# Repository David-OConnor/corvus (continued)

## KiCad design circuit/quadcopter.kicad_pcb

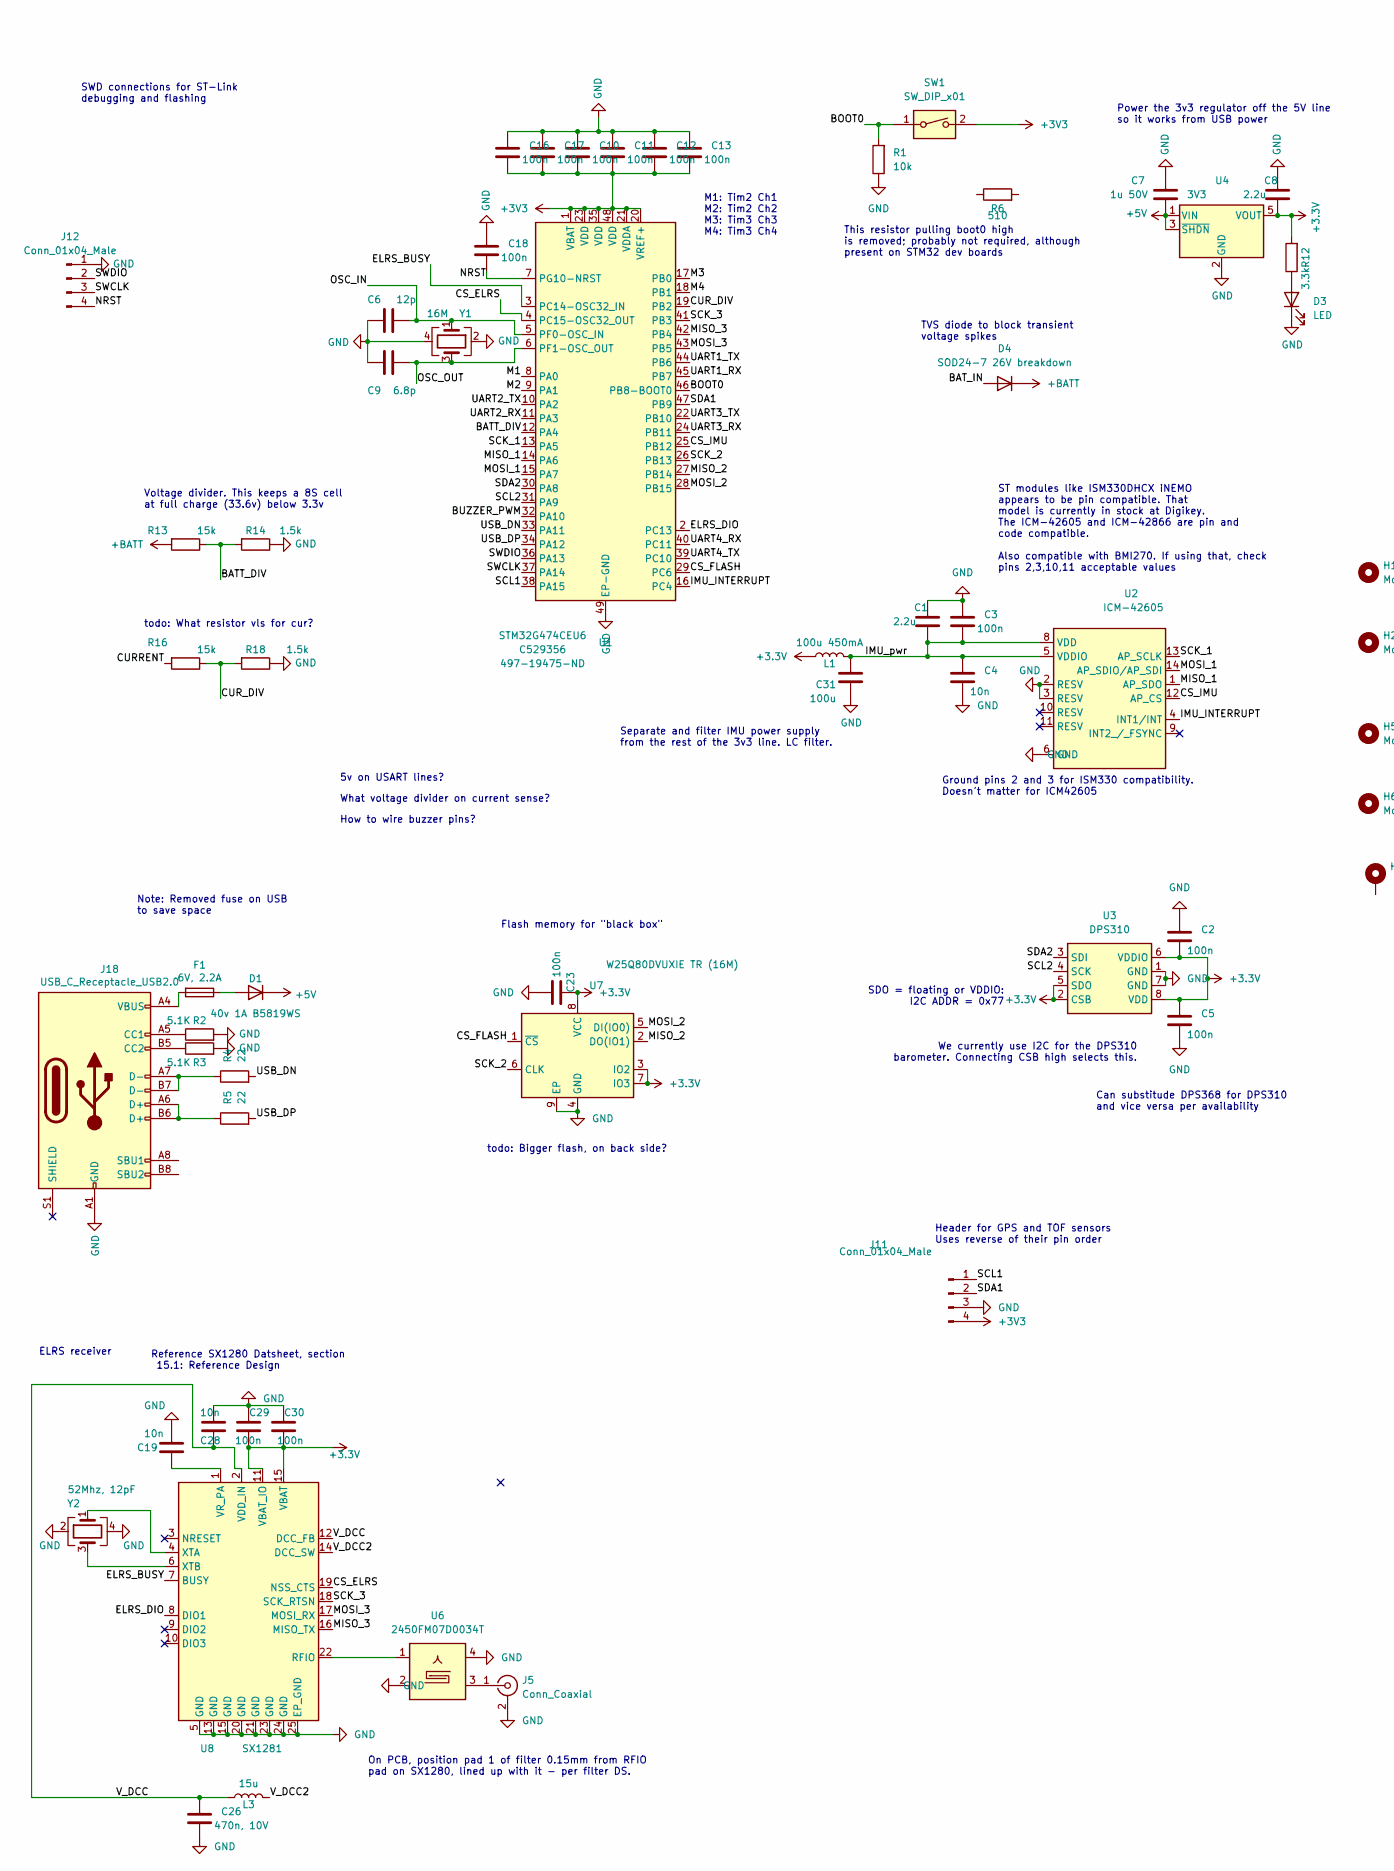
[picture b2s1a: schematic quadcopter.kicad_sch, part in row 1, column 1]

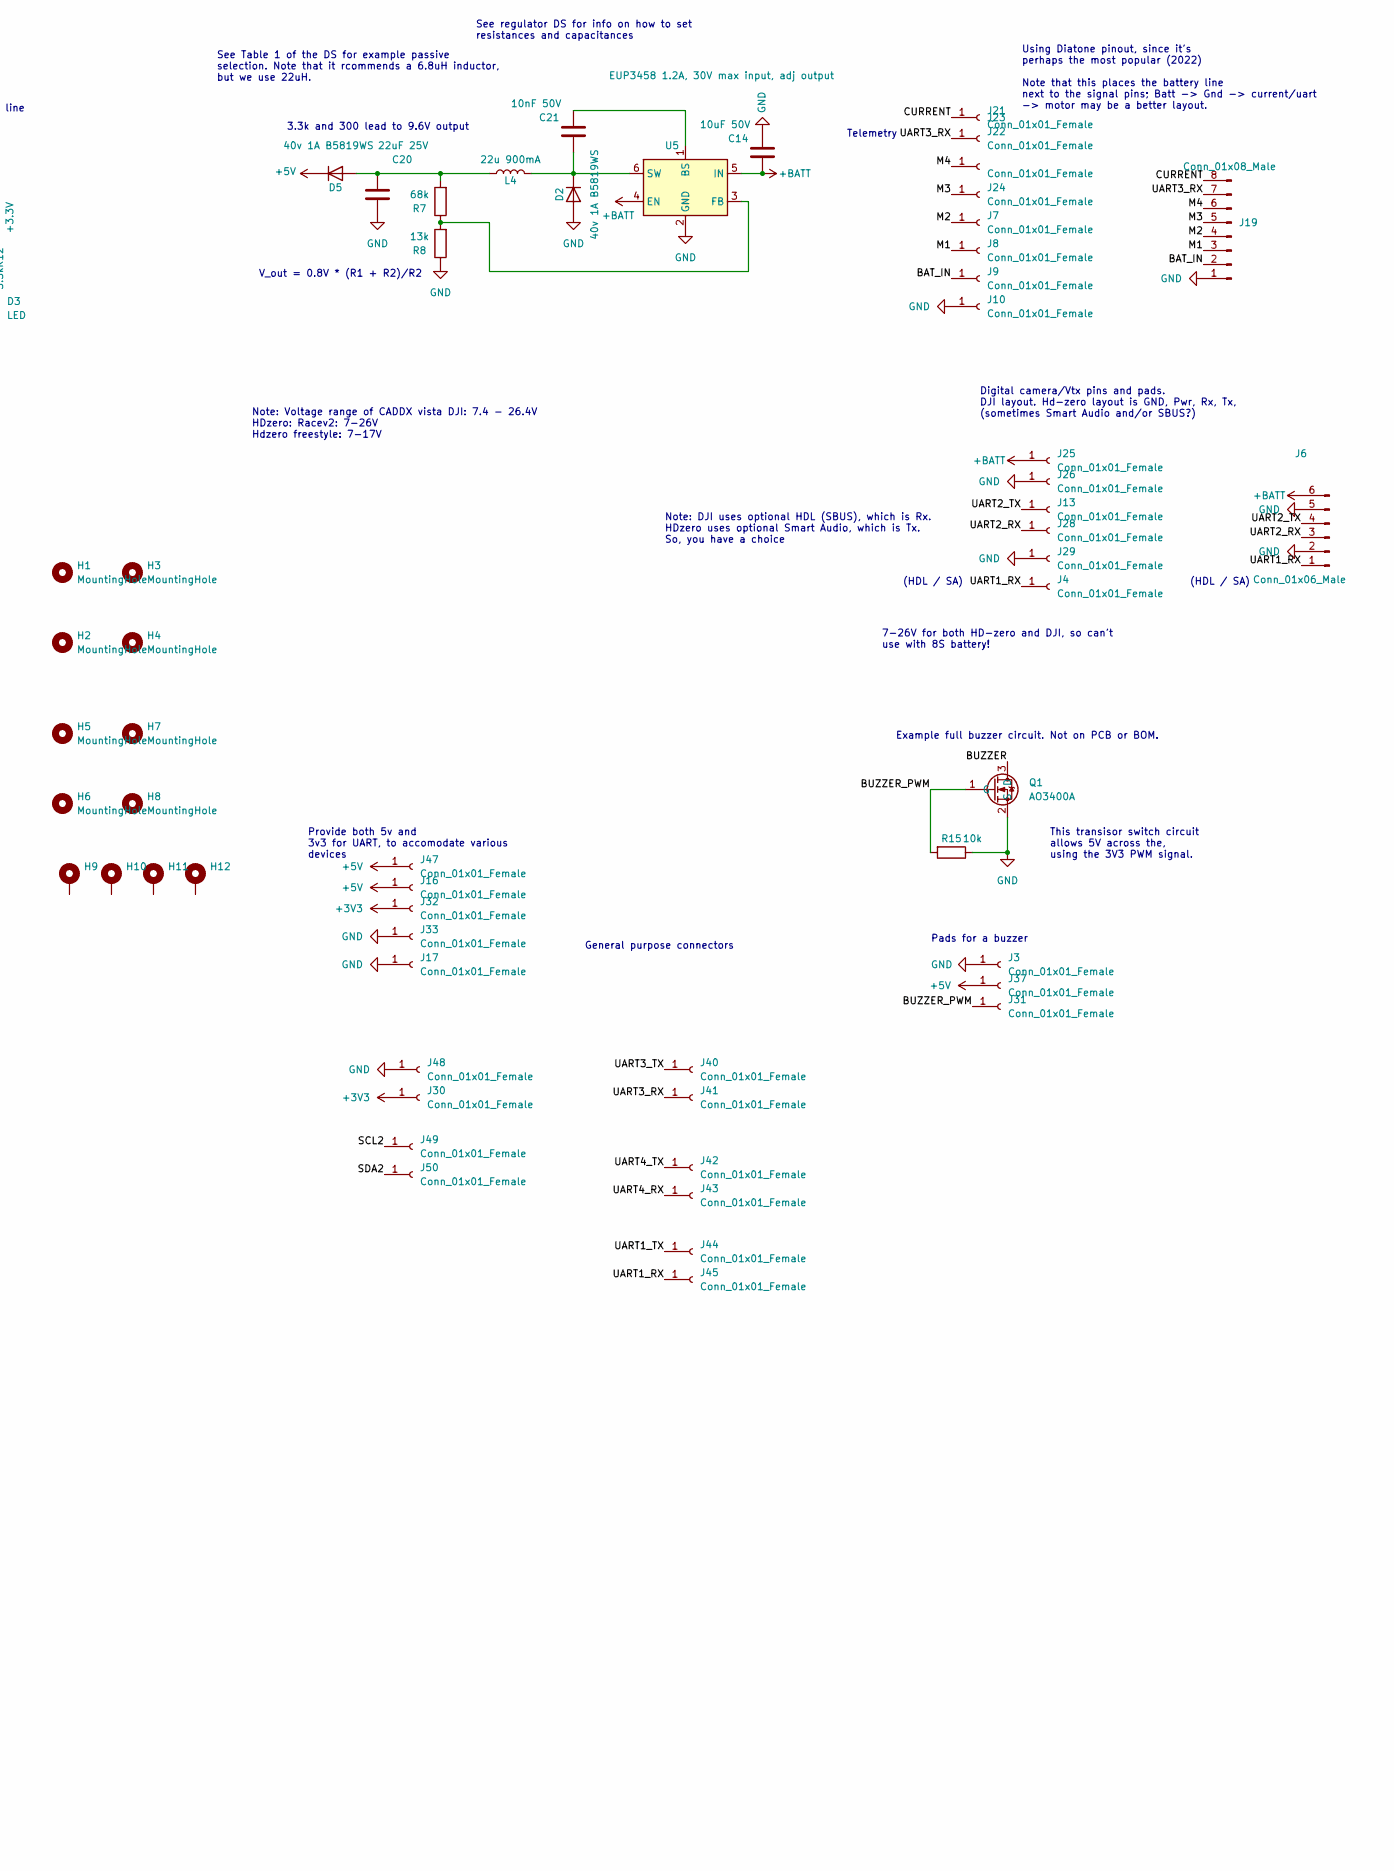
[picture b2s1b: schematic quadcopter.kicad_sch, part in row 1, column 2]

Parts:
C1, C8: 2.2u; C_0402_1005Metric; LCSC C12530
C2, C3, C5, C10, C11, C12, C13, C16, C17, C18, C23, C29, C30: 100n; C_0402_1005Metric; LCSC C1525
C4, C19, C28: 10n; C_0402_1005Metric; LCSC C15195
C6: 12p; C_0402_1005Metric; LCSC C1547
C7: 1u 50V; C_0603_1608Metric; LCSC C15849
C9: 6.8p; C_0402_1005Metric; LCSC C1576
C14: 10uF 50V; C_0805_2012Metric; LCSC C440198
C20: 22uF 25V; C_0805_2012Metric; LCSC C602037
C21: 10nF 50V; C_0402_1005Metric; LCSC C15195
C26: 470n, 10V; C_0402_1005Metric; LCSC C47339
C31: 100u; C_0805_2012Metric; LCSC C141660
D1, D2, D5: 40v 1A B5819WS; D_SOD-323; LCSC C22624
D3: LED; LED_0603_1608Metric; LCSC C205443
D4: SOD24-7 26V breakdown; D_SOD-323; Digikey 31-SD24-7TR-ND
F1: 6V, 2.2A; Fuse_0805_2012Metric; LCSC C70062
H1, H2, H3, H4, H5, H6, H7, H8: MountingHole; MountingHole_3.2mm_M3
H9, H10, H11, H12: MountingHole_Pad; Mouse bites_7mm
J3, J4, J13, J25, J26, J28, J29, J31, J37: Conn_01x01_Female; TestPoint_Pad_1.5x1.5mm
J5: Conn_Coaxial; U.FL_Hirose_U.FL-R-SMT-1_Vertical; Part Hirose U.FL-R-SMT-1(80); LCSC C88374
J6: Conn_01x06_Male; JST_SH_BM06B-SRSS-TB_1x06-1MP_P1.00mm_Vertical; LCSC C160405
J7, J8, J9, J10, J16, J17, J21, J22, J23, J24, J30, J32, J33, J40, J41, J42, J43, J44, J45, J47, J48, J49, J50: Conn_01x01_Female; TestPoint_Pad_2.0x2.0mm
J11: Conn_01x04_Male; JST_SH_SM04B-SRSS-TB_1x04-1MP_P1.00mm_Horizontal
J12: Conn_01x04_Male; JST PH staggered for 1x04 2mm
J18: USB_C_Receptacle_USB2.0; USB_C_Receptacle_XKB_U262-16XN-4BVC11; LCSC C167321
J19: Conn_01x08_Male; JST_SH_SM08B-SRSS-TB_1x08-1MP_P1.00mm_Horizontal; LCSC C160407
L1: 100u 450mA; SMNR4020 inductor; LCSC C467068
L3: 15u; L_0805_2012Metric; LCSC C154120
L4: 22u 900mA; SMNR4020 inductor; LCSC C88254
Q1: AO3400A; SOT-23; Digikey 785-1000-1-ND
R1, R15: 10k; R_0402_1005Metric; LCSC C25744
R2, R3: 5.1K; R_0402_1005Metric; LCSC C25905
R4, R5: 22; R_0402_1005Metric; LCSC C25092
R6: 510; R_0402_1005Metric; LCSC C25123
R7: 68k; R_0402_1005Metric; LCSC C36871
R8: 13k; R_0603_1608Metric; LCSC C22797
R12: 3.3k; R_0402_1005Metric; LCSC C25890
R13, R16: 15k; R_0402_1005Metric; LCSC C25756
R14, R18: 1.5k; R_0402_1005Metric; LCSC C25867
SW1: SW_DIP_x01; SW-SMD-2_3.6x6.0x8.0; LCSC C354946
U1: STM32G474CEU6; QFN-48-1EP_7x7mm_P0.5mm_EP5.6x5.6mm; LCSC C529356
U2: ICM-42605; LGA-14_3x2.5mm_P0.5mm_LayoutBorder3x4y; Digikey 1428-1152-2-ND
U3: DPS310; Bosch_LGA-8_2x2.5mm_P0.65mm_ClockwisePinNumbering; Digikey DPS310XTSA1TR-ND
U4: 3V3; TSOT-23-5; Part NATLINEAR LN1134A332MR-G; LCSC C141419
U5: EUP3458 1.2A, 30V max input, adj output; TSOT-23-6; LCSC C89300
U6: 2450FM07D0034T; 2450FM07D0034; Mouser 609-2450FM07D0034T
U7: W25Q80DVUXIE TR (16M); USON-8_2.0x3.0mm_P0.5mm; Digikey W25Q80DVUXIETR-ND
U8: SX1281; QFN-24-1EP_4x4mm_P0.5mm_EP2.6x2.6mm; Digikey SX1281IMLTRTTR-ND
Y1: 16M; Crystal_SMD_2016-4Pin_2.0x1.6mm; LCSC C254300
Y2: 52Mhz, 12pF; Crystal_SMD_3225-4Pin_3.2x2.5mm; Digikey FL520WFMT1TR-ND

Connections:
+5V: C7.2, D1.1 (K), D5.1 (K), J16.1, J37.1, J47.1, U4.1 (VIN), U4.3 (~SHDN)
+BATT: C14.2, D4.1 (K), J6.6, J25.1, R13.2, U5.4 (EN), U5.5 (IN)
/BATT_DIV: R13.1, R14.2, U1.12 (PA4)
/BAT_IN: D4.2 (A), J9.1, J19.2
/BOOT0: R1.2, SW1.1, U1.46 (PB8-BOOT0)
/BUZZER_PWM: J31.1, Q1.1 (G), R15.2, U1.32 (PA10)
/CS_ELRS: U1.4 (PC15-OSC32_OUT), U8.19 (NSS_CTS)
/CS_FLASH: U1.29 (PC6), U7.1 (~CS)
/CS_IMU: U1.25 (PB12), U2.12 (AP_CS)
/CURRENT: J19.8, J21.1, R16.2
/CUR_DIV: R16.1, R18.2, U1.19 (PB2)
/ELRS_BUSY: U1.3 (PC14-OSC32_IN), U8.7 (BUSY)
/ELRS_DIO: U1.2 (PC13), U8.8 (DIO1)
/IMU_INTERRUPT: U1.16 (PC4), U2.4 (INT1/INT)
/IMU_pwr: C1.2, C3.2, C4.1, C31.2, L1.2, U2.5 (VDDIO), U2.8 (VDD)
/M1: J8.1, J19.3, U1.8 (PA0)
/M2: J7.1, J19.4, U1.9 (PA1)
/M3: J19.5, J24.1, U1.17 (PB0)
/M4: J19.6, J23.1, U1.18 (PB1)
/MISO_1: U1.14 (PA6), U2.1 (AP_SDO)
/MISO_2: U1.27 (PB14), U7.2 (DO(IO1))
/MISO_3: U1.42 (PB4), U8.16 (MISO_TX)
/MOSI_1: U1.15 (PA7), U2.14 (AP_SDIO/AP_SDI)
/MOSI_2: U1.28 (PB15), U7.5 (DI(IO0))
/MOSI_3: U1.43 (PB5), U8.17 (MOSI_RX)
/NRST: C18.2, J12.4, U1.7 (PG10-NRST)
/OSC_IN: C6.2, U1.5 (PF0-OSC_IN), Y1.1
/OSC_OUT: C9.2, U1.6 (PF1-OSC_OUT), Y1.3
/SCK_1: U1.13 (PA5), U2.13 (AP_SCLK)
/SCK_2: U1.26 (PB13), U7.6 (CLK)
/SCK_3: U1.41 (PB3), U8.18 (SCK_RTSN)
/SCL1: J11.1, U1.38 (PA15)
/SCL2: J49.1, U1.31 (PA9), U3.4 (SCK)
/SDA1: J11.2, U1.47 (PB9)
/SDA2: J50.1, U1.30 (PA8), U3.3 (SDI)
/SWCLK: J12.3, U1.37 (PA14)
/SWDIO: J12.2, U1.36 (PA13)
/UART1_RX: J4.1, J6.1, J45.1, U1.45 (PB7)
/UART1_TX: J44.1, U1.44 (PB6)
/UART2_RX: J6.3, J28.1, U1.11 (PA3)
/UART2_TX: J6.4, J13.1, U1.10 (PA2)
/UART3_RX: J19.7, J22.1, J41.1, U1.24 (PB11)
/UART3_TX: J40.1, U1.22 (PB10)
/UART4_RX: J43.1, U1.40 (PC11)
/UART4_TX: J42.1, U1.39 (PC10)
/USB_DN: R4.2, U1.33 (PA11)
/USB_DP: R5.2, U1.34 (PA12)
/V_DCC: C26.1, C28.2, L3.1, U8.2 (VDD_IN), U8.12 (DCC_FB)
/V_DCC2: L3.2, U8.14 (DCC_SW)
unnamed: C19.2, U8.1 (VR_PA)
unnamed: C20.1, D5.2 (A), L4.1, R7.2
unnamed: C21.1, U5.1 (BS)
unnamed: C21.2, D2.1 (K), L4.2, U5.6 (SW)
unnamed: D1.2 (A), F1.1
unnamed: D3.2 (A), R12.1
unnamed: F1.2, J18.A4 (VBUS), J18.A9 (VBUS), J18.B4 (VBUS), J18.B9 (VBUS)
unnamed: J5.1 (In), U6.3
unnamed: J18.A5 (CC1), R2.1
unnamed: J18.A6 (D+), J18.B6 (D+), R5.1
unnamed: J18.A7 (D-), J18.B7 (D-), R4.1
unnamed: J18.B5 (CC2), R3.1
unnamed: R7.1, R8.2, U5.3 (FB)
unnamed: U6.1, U8.22 (RFIO)
unnamed: U8.4 (XTA), Y2.1
unnamed: U8.6 (XTB), Y2.3

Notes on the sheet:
(HDL / SA)
todo: What resistor vls for cur?
5v on USART lines?
Telemetry
3.3k and 300 lead to 9.6V output
How to wire buzzer pins?
M1: Tim2 Ch1 M2: Tim2 Ch2 M3: Tim3 Ch3 M4: Tim3 Ch4
See regulator DS for info on how to set resistances and capacitances
General purpose connectors
Voltage divider. This keeps a 8S cell at full charge (33.6v) below 3.3v
todo: Bigger flash, on back side?
Digital camera/Vtx pins and pads. DJI layout. Hd-zero layout is GND, Pwr, Rx, Tx, (sometimes Smart Audio and/or SBUS?)
Note: Removed fuse on USB to save space
On PCB, position pad 1 of filter 0.15mm from RFIO pad on SX1280, lined up with it - per filter DS.
Reference SX1280 Datsheet, section 15.1: Reference Design
We currently use I2C for the DPS310 barometer. Connecting CSB high selects this.
Separate and filter IMU power supply from the rest of the 3v3 line. LC filter.
V_out = 0.8V * (R1 + R2)/R2
This transisor switch circuit allows 5V across the, using the 3V3 PWM signal.
Provide both 5v and 3v3 for UART, to accomodate various devices
See Table 1 of the DS for example passive selection. Note that it rcommends a 6.8uH inductor, but we use 22uH.
TVS diode to block transient voltage spikes
ST modules like ISM330DHCX iNEMO appears to be pin compatible. That model is currently in stock at Digikey. The ICM-42605 and ICM-42866 are pin and code compatible. Also compatible with BMI270. If using that, check pins 2,3,10,11 acceptable values
Example full buzzer circuit. Not on PCB or BOM.
This resistor pulling boot0 high is removed; probably not required, although present on STM32 dev boards
SWD connections for ST-Link debugging and flashing
Ground pins 2 and 3 for ISM330 compatibility. Doesn't matter for ICM42605
Using Diatone pinout, since it's perhaps the most popular (2022) Note that this places the battery line next to the signal pins; Batt -> Gnd -> current/uart -> motor may be a better layout.
What voltage divider on current sense?
Flash memory for "black box"
Header for GPS and TOF sensors Uses reverse of their pin order
Note: Voltage range of CADDX vista DJI: 7.4 - 26.4V HDzero: Racev2: 7-26V Hdzero freestyle: 7-17V
ELRS receiver
Note: DJI uses optional HDL (SBUS), which is Rx. HDzero uses optional Smart Audio, which is Tx. So, you have a choice
Pads for a buzzer
Can substitude DPS368 for DPS310 and vice versa per availability
SDO = floating or VDDIO: I2C ADDR = 0x77
Power the 3v3 regulator off the 5V line so it works from USB power
7-26V for both HD-zero and DJI, so can't use with 8S battery!

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
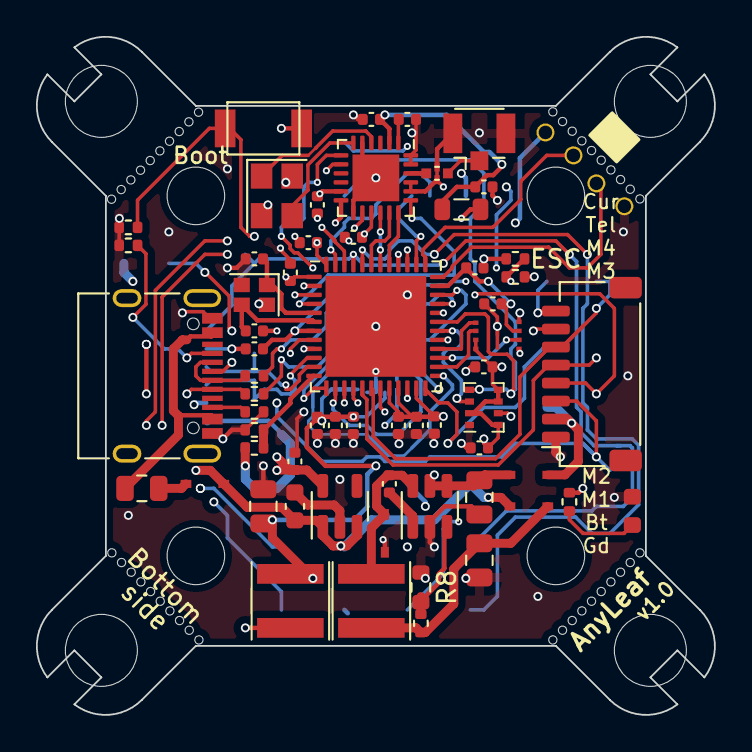
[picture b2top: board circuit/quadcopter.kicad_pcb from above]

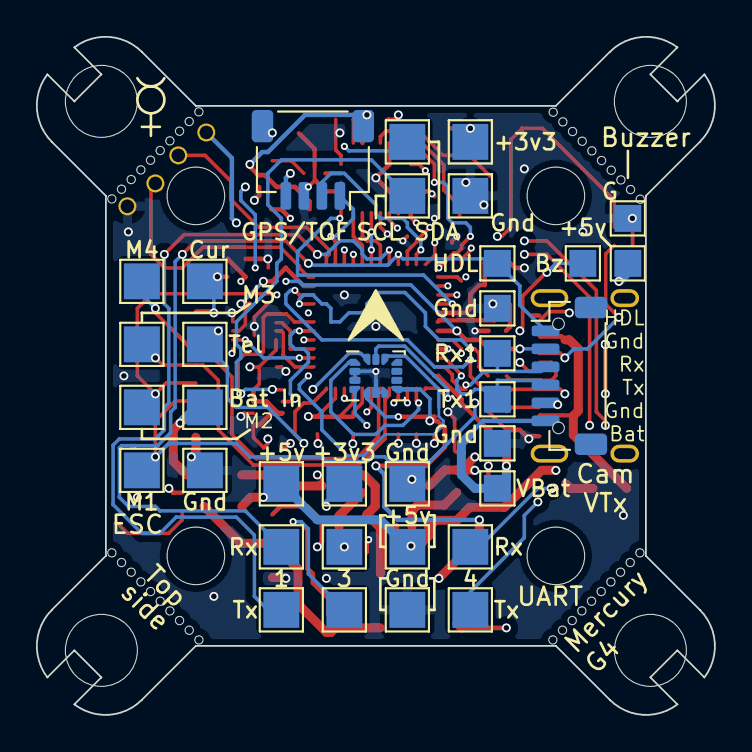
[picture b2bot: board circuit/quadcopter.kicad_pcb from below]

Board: 4 copper layers, 37.7 x 37.7 mm, 108 parts (35 on the bottom side), 67 nets.

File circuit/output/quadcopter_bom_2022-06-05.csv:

Comment,Designator,Footprint,LCSC
"2.2u","C1,C8,C22","Capacitor_SMD:C_0402_1005Metric","C12530"
"10uF 50V","C14","Capacitor_SMD:C_0805_2012Metric","C440198"
"100n","C2,C3,C5,C10,C11,C12,C13,C16,C17,C18,C23,C29,C30","Capacitor_SMD:C_0402_1005Metric","C1525"
"22uF 25V","C20","Capacitor_SMD:C_0805_2012Metric","C45783"
"10nF 50V","C21","Capacitor_SMD:C_0402_1005Metric","C15195"
"470n, 10V","C26","Capacitor_SMD:C_0402_1005Metric","C47339"
"100u","C31","Capacitor_SMD:C_0805_2012Metric","C141660"
"10n","C4,C19,C28","Capacitor_SMD:C_0402_1005Metric","C15195"
"12p","C6","Capacitor_SMD:C_0402_1005Metric","C1547"
"1u 50V","C7,C15","Capacitor_SMD:C_0603_1608Metric","C15849"
"6.8p","C9","Capacitor_SMD:C_0402_1005Metric","C1576"
"40v 1A B5819WS","D1,D2,D5","Diode_SMD:D_SOD-323","C22624"
"LED","D3","LED_SMD:LED_0603_1608Metric","C205443"
"SOD24-7 26V breakdown","D4","Diode_SMD:D_SOD-323",""
"6V, 2.2A","F1","Fuse:Fuse_0805_2012Metric","C70062"
"Conn_01x04_Male","J11","Connector_JST:JST_SH_SM04B-SRSS-TB_1x04-1MP_P1.00mm_Horizontal",""
"Conn_01x04_Male","J12","Anyleaf_Shared:JST PH staggered for 1x04 2mm",""
"USB_C_Receptacle_USB2.0","J18","Connector_USB:USB_C_Receptacle_XKB_U262-16XN-4BVC11","C167321"
"Conn_01x08_Male","J19","Connector_JST:JST_SH_SM08B-SRSS-TB_1x08-1MP_P1.00mm_Horizontal","C160407"
"Conn_01x01_Female","J3,J4,J13,J25,J26,J28,J29,J31,J37","TestPoint:TestPoint_Pad_1.5x1.5mm",""
"Conn_Coaxial","J5","Connector_Coaxial:U.FL_Hirose_U.FL-R-SMT-1_Vertical","C88374"
"Conn_01x01_Female","J7,J8,J9,J10,J16,J17,J21,J22,J23,J24,J30,J32,J33,J40,J41,J42,J43,J44,J45,J47,J48,J49,J50","TestPoint:TestPoint_Pad_2.0x2.0mm",""
"100u 450mA","L1","Anyleaf_Shared:SMNR4020 inductor","C467068"
"15u","L3","Inductor_SMD:L_0805_2012Metric","C154120"
"22u 900mA","L4","Anyleaf_Shared:SMNR4020 inductor","C88254"
"10k","R1","Resistor_SMD:R_0402_1005Metric","C25744"
"3.3k","R12","Resistor_SMD:R_0402_1005Metric","C25890"
"15k","R13,R16","Resistor_SMD:R_0402_1005Metric","C25756"
"1.5k","R14,R18","Resistor_SMD:R_0402_1005Metric","C25867"
"5.1K","R2,R3","Resistor_SMD:R_0402_1005Metric","C25905"
"22","R4,R5","Resistor_SMD:R_0402_1005Metric","C25092"
"3.3K","R7","Resistor_SMD:R_0402_1005Metric","C25890"
"300","R8","Resistor_SMD:R_0402_1005Metric","C25102"
"SW_DIP_x01","SW1","Anyleaf_Shared:SW-SMD-2_3.6x6.0x8.0","C354946"
"STM32G474CEU6","U1","Package_DFN_QFN:QFN-48-1EP_7x7mm_P0.5mm_EP5.6x5.6mm","C529356"
"ICM-42605","U2","Package_LGA:LGA-14_3x2.5mm_P0.5mm_LayoutBorder3x4y","C2655099"
"DPS310","U3","Package_LGA:Bosch_LGA-8_2x2.5mm_P0.65mm_ClockwisePinNumbering",""
"3V3","U4","Package_TO_SOT_SMD:TSOT-23-5","C141419"
"EUP3458 1.2A, 30V max input, adj output","U5","Package_TO_SOT_SMD:TSOT-23-6","C89300"
"2450FM07D0034T","U6","Anyleaf_Shared:2450FM07D0034",""
"W25Q80DVUXIE TR (16M)","U7","Anyleaf_Shared:USON-8_2.0x3.0mm_P0.5mm",""
"SX1281","U8","Package_DFN_QFN:QFN-24-1EP_4x4mm_P0.5mm_EP2.6x2.6mm","C2151551"
"5v, 500mA","U9","Package_TO_SOT_SMD:TSOT-23-5","C13417"
"16M","Y1","Crystal:Crystal_SMD_2016-4Pin_2.0x1.6mm","C254300"
"52Mhz, 12pF","Y2","Crystal:Crystal_SMD_3225-4Pin_3.2x2.5mm",""

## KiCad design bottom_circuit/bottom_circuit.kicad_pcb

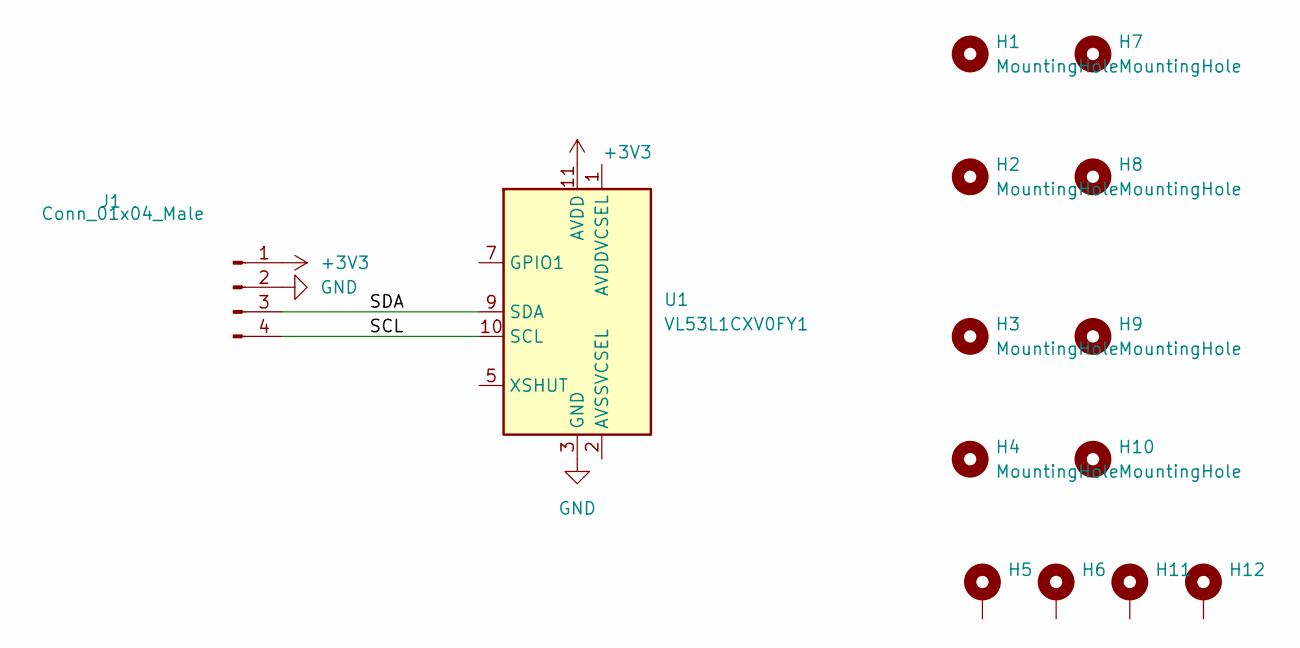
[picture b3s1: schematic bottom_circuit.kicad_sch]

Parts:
H1, H2, H3, H4, H7, H8, H9, H10: MountingHole; MountingHole_3.2mm_M3
H5, H6, H11, H12: MountingHole_Pad; Mouse bites_7mm
J1: Conn_01x04_Male; JST_SH_SM04B-SRSS-TB_1x04-1MP_P1.00mm_Horizontal
U1: VL53L1CXV0FY1; ST_VL53L1x

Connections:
+3V3: J1.1, U1.11 (AVDD)
/SCL: J1.4, U1.10 (SCL)
/SDA: J1.3, U1.9 (SDA)
GND: J1.2, U1.3 (GND), U1.4 (GND), U1.6 (GND), U1.12 (GND)

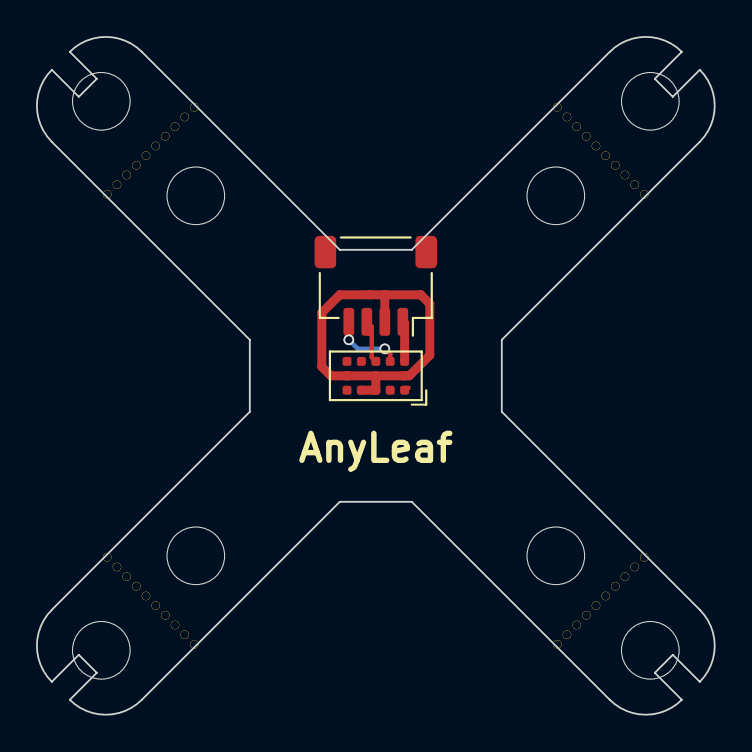
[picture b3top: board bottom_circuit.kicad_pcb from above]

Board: 2 copper layers, 37.7 x 37.7 mm, 14 parts (0 on the bottom side), 4 nets.

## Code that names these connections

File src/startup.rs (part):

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    let mut spi1 = Spi::new(dp.SPI1, imu_spi_cfg, imu_baud_div);

    #[cfg(feature = "mercury-h7")]
        let mut cs_imu = Pin::new(Port::C, 4, PinMode::Output);
    #[cfg(feature = "g4")]
        let mut cs_imu = Pin::new(Port::B, 12, PinMode::Output);

    cs_imu.set_high();

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    // See ELRS `SX1280_hal.cpp`, `init` fn for pin setup.
    // todo: Move this as approp.
    // Used to trigger a a control-data-received update based on new ELRS data.
    let elrs_busy = Pin::new(Port::C, 14, PinMode::Input);

    // todo: Put elrs_dio back. Currently disabled since we have accidentally shorted it to SCL2.
    // let mut elrs_dio = Pin::new(Port::C, 13, PinMode::Input);
    // elrs_dio.enable_interrupt(Edge::Rising);
    let mut cs_elrs = Pin::new(Port::C, 15, PinMode::Input);
    cs_elrs.set_high();

    // We use SPI3 for flash. // todo: Find max speed and supported modes.
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        let flash_pin = 10;
    #[cfg(not(feature = "h7"))]
        let flash_pin = 6;
    let mut cs_flash = Pin::new(Port::C, flash_pin, PinMode::Output);
    cs_flash.set_high();

    // We use I2C for the TOF sensor.(?)
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
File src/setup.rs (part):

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    spi_flash: &mut SpiFlash,
    i2c_mag: &mut I2cMag,
    i2c_baro: &mut I2cBaro,
    cs_imu: &mut Pin,
    cs_flash: &mut Pin,
    clock_cfg: &Clocks,
) -> (SystemStatus, baro::Altimeter) {
    let mut system_status = SystemStatus::default();
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            let rcc = unsafe { &(*pac::RCC::ptr()) };

            // Some or all of these lines are required to prevent strange
            // behavior of the ELRS MCU; likely due to JTAG behavior of PB3 and 4.
            rcc.apb1enr2.modify(|_, w| w.ucpd1en().set_bit());
            rcc.apb1enr1.modify(|_, w| w.pwren().set_bit());
            rcc.apb1enr2.modify(|_, w| w.ucpd1en().set_bit());
            pwr.cr3.modify(|_, w| w.ucpd1_dbdis().set_bit());

            // Undo settings on PB3 and PB4 that are due to initial debug-pin config.
            uart_crsf_tx.pull(Pull::Floating);
            uart_crsf_rx.pull(Pull::Floating);
            uart_crsf_tx.output_speed(OutputSpeed::Low);
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        if #[cfg(feature = "h7")] {
            // Config of USB pins on H743. We don't need this on G4 or H723
            let _usb_dm = Pin::new(Port::A, 11, PinMode::Alt(10));
            let _usb_dp = Pin::new(Port::A, 12, PinMode::Alt(10));
        }
    }

    let mut cs_imu = Pin::new(PIN_CS_IMU.0, PIN_CS_IMU.1, PinMode::Output);
    cs_imu.set_high();

    let imu_spi_cfg = SpiConfig {
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    let spi_flash = Spi::new(spi_flash_pac, Default::default(), BaudRate::Div2);

    #[cfg(feature = "h7")]
    let mut cs_flash = Pin::new(Port::E, 11, PinMode::Output);
    #[cfg(feature = "g4")]
    let mut cs_flash = Pin::new(Port::A, 0, PinMode::Output);

    cs_flash.set_high();

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
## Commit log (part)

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2022-04-23 Added start to madgwick filter, based on original impl
2022-04-23 More work on Madgwick
2022-04-23 Madgwick now compiles
2022-04-23 More work on fusion
2022-04-25 Added MSP module start
2022-04-25 Add projection matrix to OSD.
2022-04-27 Fixed a number of errors in recently-added attitude and MSP code
2022-04-28 Cleaned up Madgwick API a bit
2022-04-29 Reflowed CRSF flow
2022-04-30 Progress on CRSF DMA buf management
2022-05-01 CRSF channel data rx now works
2022-05-01 Map CRSF data directly to useful controls
2022-05-01 Integrated ctrl inputs to rest of program
2022-05-03 Arming with combination throttle=idle and switch set up
2022-05-03 Added lost link logic
2022-05-05 replaced pads with header for ST-link connection.
2022-05-06 More work on sx1280 driver/elrs
2022-05-06 More work on ELRS
2022-05-07 More work
2022-05-07 Added hwtimer module for ELRS
2022-05-10 Started on USB serialization
2022-05-10 moved arm and lost link code to new safety mod
2022-05-12 Fixed a number of errors on USB serial preflight
2022-05-15 Misc changes
2022-05-17 PID constant adjustment, plus added throttle PID attenuation
2022-05-20 More work on USB config via preflight software
2022-05-21 Adjuseted USB sending code to remove Packet struct, and pass quaternion for attitude
2022-05-31 Refactored flight ctrls by airframe type. Added template for flying wing
2022-05-31 Added basic flight control code for flying wing
2022-06-02 Refactored baro/alt module, including applying calibration and temp comp
2022-06-02 Cleanup to altimeter
2022-06-05 Basic elevon servo control working
2022-06-06 More work on H7 board layout
2022-06-08 refactored state into sep module; moved some code to statevolatile that were individual resources.
2022-06-08 Set up ADC measurements
2022-06-09 More work on routing
2022-06-14 More work on fixing code for H7 variant
2022-06-15 Misc board cleanup for g4 and h7. Misc flying-wing (mainly servo) changes to code
2022-06-16 More work on H7 variant code
2022-06-17 More work on board. Removed motor args from set power fns
2022-06-18 Started switch to PID setup where starting point is prev control settings; no 0
2022-06-20 Added link stats to preflight
2022-06-21 added tx pwr enum, and pass to preflight
2022-06-26 H7 fixes
2022-06-27 Work on H7 USB
2022-06-28 Cleanup to motor/tim refactor
2022-06-28 Adjustments to gain on ahrs
2022-07-03 More work on H7 board. Removed ctrl mix from firmware
2022-07-06 Added timer ARR/PSC and clock config speeds for H743@480Mhz, H723 at 520 and 550Mhz
2022-07-07 G4 model: Removed 10v line and prev 5v reg
2022-07-09 Added code for in-flight PID tuning.
2022-07-16 More work on airborne PID adjustment
2022-07-16 Removed ELRScode stubs
2022-07-16 work on MSP/OSD
2022-07-17 More work on OSD/MSP
2022-07-17 more OSDwork
2022-07-18 Tweaks to OSD
2022-07-22 Use static buffers and DMA for MSP
2022-07-23 Use single DMA buffer for OSD
2022-07-25 Restructured/renamed project
2022-07-25 refactored autopilot into sep module
2022-07-26 More cleanup, including commenting-out MSPcommands, using lat/lon names for locations, adding offboard flash setup code, and more
2022-07-26 Started work on refactor of PIDs to have cleaner passing between outer to inner loops
2022-07-26 refactored autopilot; basic alt hold modes impl
2022-07-27 minor reorg in autopilot ordering
2022-07-28 Work on direct-to-pt autopilot on fixed wing
2022-07-29 Added AP mode status to OSD
2022-07-29 Minor refactoring, including removing command state
2022-08-01 Refactoring start of lost link,ie to use autopilot modes
2022-08-02 Lots of work impling autopilot from switches
2022-08-11 Added set servo wing position from preflight
2022-08-11 More work on servo posits
2022-08-16 More work on fixed/quad feature gate
2022-08-17 Fixed wing and Quad targets now compile
2022-08-18 Consolidated/feature-gated some PIDcontrols
2022-08-31 Started cleaning up broken FC/autopilot code from prev revision
2022-08-31 Now copmiles, again
2022-09-04 Use external lin alg lib. More work converting to system status API
2022-09-05 Changed servo code to be centered on 1.5ms up time; cleaned up changes from last few compiles
2022-09-09 More cleanup
2022-09-14 More work on attitude-based controls
2022-09-14 more work on attitude controls
2022-09-18 Misc minor cleanup/regorg of flight controls, including removing apply_ctrls
2022-09-19 More work on att ctrls
2022-09-20 More cleanup after sensor refactor
2022-09-20 Added setup code for mag
2022-09-22 More work on flt ctrls logic
2022-09-23 Refactored to make hte new attitude-based controls API primary. Work on it
2022-09-24 Added sequencing of DMA writes and read for baro and ext sensors
2022-09-24 Tweaks to flight ctrl logic. Add filters to ctrl effectiveness
2022-09-25 Added a flight control model script
2022-09-25 Convert DMA buf for baro to readings in TC ISR
2022-09-25 work on bidir DSHOT
2022-09-28 Added ability to have controls only armed for fixed-wing; added servo safety mechanism to hard set pin status up
2022-09-28 Use 2 switches for ctrl, motor arm on fixed
2022-09-29 Some tweaks
2022-10-01 Moved motor direction code to main loop, with some apt guards; attempt at getting it working
2022-10-04 Added code to log power mapping
2022-10-06 Set up RPM PID
2022-10-09 More work on our flight control logic, including a by-default continuous angular accel, with discontinuity as required
2022-10-12 Clean up work
2022-10-13 Made motor/servo timer-pin assignment more flexible and explicit
2022-10-14 Added drag coeff logging and use
2022-10-17 Misc cleanup, including more clear/consolidated bidir DSHOT code
2022-10-18 test
2022-10-26 Misc work trying to figure out what's wrong with the program
2022-10-26 Another attempt at non-circular CRSF
2022-10-27 back to serial crsf
2022-10-29 Some cleanup re params module, and update and imu loop incrementeres
2022-11-01 Misc TS
2022-11-01 More tweaks/TS
2022-11-01 Misc, including adding a fault flag for RF data
2022-11-03 TS crsf
2022-11-03 More TS on CRSF
2022-11-03 Some init order etc adjustment
2022-11-03 Motor dir setting now works. Refactored it adn related code out of idle, and to teh end of main, with some notes
2022-11-04 A reasonable amount of work done on DSHOT bidir
2022-11-05 more work on bidir dshot
2022-11-09 Improvements to USB/CRC check. Working through CRSF clipped bytes problems
2022-11-10 Added customization flight ctrl loop ratio based on IMU
2022-11-11 Updated to use new HAL DMA api
2022-11-11 Switched to new HAL free-fn DMA interrupt clear
2022-11-11 Misc improvements to scheduling and CRSF
2022-11-15 Major overhaul of timer logic to use only a single DSHOT timer for both H7 and G4
2022-11-17 Misc cleanup, including getting DSHOT working again, and adding PU on the CRSF Rx lines
2022-11-18 Added parsing RPM and telem from Bidir dshot
2022-11-18 First moves on bitbanged DSHOT reception
2022-11-19 lots of work on RPM reception
2022-11-20 Div not mul by DT in flight ctrl logic. Use IMU DT. Use measured RPM, not commanded in right place when commanding RPM
2022-11-21 Some work on RPM reception, and work on removing locks from CRSF
2022-11-30 Status added for SPI flash
2022-12-04 Some progress on timer read burst dma
2022-12-08 Fixed errors on pressure. Now produces almost reasonable readings, but still some bugs, and unable to work on DMA
2022-12-09 Store alt MSL from pressure. Fixed errors in altimeter coeff parsing
2022-12-10 Some refactoring of motor and servo timer setup; removed warmup time
2022-12-11 Cleaned up prev RPM reading approaches. New approach reads; working on interpreting results
2022-12-13 Some cleanup of ARR. Work on parsing RPM recep
2022-12-14 RPM tweaks
2022-12-14 RPM reception logic should now be good; but untested on hardware
2023-01-08 More work on RPM
2023-01-11 Updated some H7 compatibility issues
2023-01-16 Restructured GCR RPM interpretation function
2023-01-16 More cleanup of RPM code, and adjusted scalers in decoding
2023-01-27 Cleaned up PAC type logic to be more consistent; esp re UART
2023-02-04 Work re new cs IMU assignment on G4 to deconflict with Motor 2
2023-02-15 Misc cleanup on flgith control logic; mainly fixed-wing
2023-02-17 RPM command code now works. Changed rpm-related state names to be more clear and explicit
2023-02-18 Work on RPMs/power to preflight
2023-02-18 In progress of major rework of state related to motors and servos
2023-02-18 More work refactoring servos/motors
2023-02-19 Now compiles again, post changeup
2023-02-19 now compiles again on fixed
2023-02-19 Switched RPM-to-accel map to polynomial coeffs
2023-02-21 misc
2023-03-04 Configure AAF filter on IMU. Configure bank sel
2023-03-05 Fixed a bug with Motor 2 RPM
2023-03-07 Some cleanup on flight control flow
2023-03-11 Cleaned up separation between CRSF decoding and corvus-specific ch data
2023-03-12 Work on CAN
2023-03-23 Misc crsf cleanup
2023-03-30 Some work
2023-03-30 Added global time counter
2023-04-01 Work on Ublox GNSS protocol
2023-04-01 Added vals for all ubx messages
2023-04-02 Implemented fix reading
2023-04-02 Added baud configuration
2023-04-03 Some cleanup on ctrl effect estimation and motorservostate
2023-04-06 Started to set up flight controls for test
2023-04-06 Work on flight ctrl logic
2023-04-09 Updated algorithm for custom d_omega on ctrl logic implemented in Py and Rust; tested in Py
2023-04-10 Moved most MCU feature gates to setuup'
2023-04-16 Added parsing of CAN id
2023-04-16 More work on CAN
2023-04-27 update cmsis dpi to use git
2023-04-29 Work decoding CAN
2023-04-30 refactored IMU code into own mod
2023-05-05 Adjusted ctrl channel reading info to be in main loop
2023-05-05 More work on CRSF refactor
2023-05-06 Fixed a numerical precision problem with att comd
2023-05-14 Some work and corrections on flight control logic. Re-organized diagnositcs
2023-05-15 more work on FC logic
2023-05-19 Updates with diff lat/lon formats etc
2023-05-26 Work updating based on new AHRS system
2023-06-02 Removed euler angles from ctrl logic. Use rots aroudn axes
2023-06-12 Some updates re AHRS API
2023-06-16 Updates to USB interrupt priority
2023-06-17 Fixed AHRS update rate
2023-06-27 Use dronecan to set up can
2023-07-07 Misc cleanup; refactored timers to own setup fn
2023-07-23 Cleanup prior to flight tests
2023-07-25 Refactor: Move main loop code to own fn. Add I term reset on 0 throttle
2023-07-25 Updated to RTIC2. Moved init to sep file
2023-07-27 Added timeouts for system status
2023-07-27 Added task duration measurements
2023-07-28 simplified timestamp code
2023-07-30 Switched to proper MSP displyport OSD. Much cleaner
2023-08-02 More work, including fixed orientation adjustment
2023-08-02 Cleaned up d term. Added I-term anti-windup. Cleaned up takeoff att lock code
2023-08-04 Progress on OSD
2023-08-05 More OSD work
2023-08-09 Misc OSD fixes and change of arm/status flow. Added system status for osd
2023-08-11 Work on integrating UART GNSS
2023-08-15 Fixed several OSD bugs
2023-08-18 Some updates re GPS pins
2023-08-18 Fixed baro
2023-08-20 Baro fixes
2023-08-20 Added I term to alt hold. Added clamp fn
2023-08-21 Work on alt hold using commanded velocity
2023-08-23 improvements to add correction mode
2023-08-25 Misc H7 fixes
2023-09-04 redid servo pwm logic
2023-09-18 Misc updates
2023-10-08 Use new timestamp API
2023-11-05 Minor cleanup, and attempt at QSPI flash
2023-12-24 Use new SPI dma cleanup
2024-01-02 Removed UART GNSS support
2024-01-02 Removed i2c mag
2024-01-12 Tweaks to add mode
2024-01-12 Work on alt hold
2024-01-13 Alt commanded code working
2024-01-13 Refactored rate controls PID
2024-01-13 sync
2024-01-14 Cleanup to the PID module
2024-01-14 Work on throttle settings
2024-01-14 Moved update commands to own flight ctrls mod
2024-01-14 Updates to baro ratio
2024-01-16 Added acc cal
2024-01-16 Use native clamp
2024-01-20 Added board_config module. Work troubleshooting H7 ADC
2024-01-21 fixed H7 ADC.
2024-01-21 More misc updates
2024-01-22 Moved some pin code to board_config
2024-01-23 More work on setup/init cleanup
2024-12-24 Added MIT license
2024-12-26 Added readme. Removedsome unused modules. Removed path deps
2024-12-26 Updated lin_alg dep
